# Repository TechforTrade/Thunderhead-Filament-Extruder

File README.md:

# Thunderhead Filament Extruder

The Thunderhead filament extruder is a  small scale extruder designed by Techfortrade that can be used for recycling PET plastic bottle flake directly into 3D printing filament. A special emphasis throughout the design has been placed on using affordable and easily attainable materials. This repository serves as a host for the documentation and code used with the machine. We are using GrabCAD Workbench for the hardware development and will place snapshots of the CAD files here on Github with each release. Current (though not necessarily stable) files can be accessed on our [GrabCAD partner space](https://workbench.grabcad.com/workbench/projects/gcvN9Xsi01SW-lFGhJRj_-4vqndCMFAaoUt_-UQBdidnVn#/space/gc8b8c582LagITdwrMEId6wysTlJX_nukUvWoRwEQ_1f4U).

#### The Thunderhead converts clean and dry PET flake into 3D printing Filament

# Table of Contents

- [Goals](#goals)
- [PET Plastic](#pet-plastic)
- [Safety and Liability](#safety-and-liability)
- [Building the Thunderhead](#building-the-thunderhead)
- [Software](#software)
- [Operation](#operation)
- [Contributing](#contributing)
- [Maintainers](#maintainers)
- [Acknowledgements](#acknowledgements)
- [License](#license)

## Goals
The Thunderhead is designed with the intent of making it possible to recycle plastic from the post consumer waste stream into 3D printing filament on a small scale with minimal start up capital required. This makes the following possible:
- Low cost 3D printing filament anywhere in the world
- Enable local capture of the value contained in waste plastic
- Access to expensive or hard to find items via 3D printing (eg. [Open Flexure Microscope](https://github.com/rwb27/openflexure_microscope))
- Small scale business opportunities without need for large amounts of capital
- Enable local recycling where it is otherwise not possible

## PET Plastic 
The Thunderhead is designed to extrude Polyethylene Terephthalate (PET or PETE) for the following reasons:

-  Prints  very well on printers such as the Retr3D
-  Easy to find nearly anywhere on the planet
-  Has good physical properties
-  Reasonably safe to work with, especially compared to ABS which often has Brominated Flame Retardants (BFR)

PET is easily identified by the following symbol usually located on the bottom on the bottle:

There are some challenges to working with PET plastic. A few these are described below. Follow the links to get more detailed information on these and other challenges:

* **Crystalization** - PET crystalizes when cooled slowly. To avoid making filament that is brittle like glass, a water bath is used.
* **Low Viscosity** - When PET melts it has a low viscosity and a low melt strength which makes it difficult to pull into a filament with an even diameter. The Thunderhead uses a cooling tube to help increase the viscosity and melt strength before the plastic leaves the extruder. The water bath also helps to 
* **Hygroscopicity** - PET pulls water out of the air and holds on to it. This water can cause problems during extrusion and printing such as air bubbles, foaming and degredation of the plastic.
* **Hydrolysis** - The polymer chains in PET can break down in the presence of water at elevated temperatures. When this happens, the viscosity of the melt is reduced, making it difficult to extrude. To Avoid this problem, the plastic flakes must be thoroughly dried just before extrusion. 

## Safety and Liability

You are responsible for your own safety. This machine is under development. Please see the text in the license regarding **Disclaimer of Warranties and Limitation of Liability**.

## Building the Thunderhead

Please refer to our [wiki](https://github.com/TechforTrade/Thunderhead-Filament-Extruder/wiki) for detailed information on building the Thunderhead. 

#### Major Tools Needed ####

Note that you don't necessarily have to own all of these tools. A local shop could do some of the work for you. Especially the lathe and milling work. See the Wiki for a more exhaustive list.

* Drill Press
* Metal Lathe - Threading the barrel and making the shaft for the gear box
* Welding (stick, oxy-acetalene, etc.) - For welding frames together
* 3D printer - Many of the complex parts in the machine are 3D printed
* Milling Machine (optional) - For milling flats into a few parts. Could be done with grinder and hand files though more time consuming.
* Horizontal band saw (optional) - For cutting stock metal to size. A hacksaw and vice will work, but will be slower.

#### Major Components of the Thunderhead - THIS NEEDS UPDATING

1. **Control Box** - Contains the power supply, Arduino, and other circuitry needed to operate the extruder. Note: The starve feeder, diameter sensors and spooler have their own control circuitry and communicate with the master Arduino via IIC.
2. **Starve Feeder**- Used to add flakes to the extruder at a constent rate. Subcomponents are:
   1. Hopper - Holdes flake ready to be extruded
   2. Vibratory Conveyer - Moves flake to the balance and keeps flake from bridging, and rat holing.
   3. Balance - Weighs out small portions of flake and then delivers them to the extruder at a constant rate. Feedback from the balance controls the vibratory conveyer.
3. **Auger Motor and Gear Box** - A large NEMA 42 stepper motor and 3:1 gear box with 3D printed gears. The stepper alows for speed control and the gearbox increases the torque on the auger.
4. **Extruder Body** - The extruder body has many components. The main components are:
   1. Feed Throat - Location where the plastic enters the barrel. Made with internal grooves to improve the feeding of the plastic into the barrel.
   2. Auger - A 1/2 in. diameter, 18 in. long wood auger used to convey the plastic through the barrel. NOTE: This is not designed for plastics extrusion and performs significantly worse than a plastic extrusion screw would. It is much less expensive though.
   3. Barrel - 1/2in I.D. DOM metal pipe through which the auger pushes the plastic. It has two heating zones that are heated by 104 watt 1/2 in. fiberglass insulated heating tape.
   4. Breaker plate - A small disk of metal with a number of holes drilled into it at the downstream end of the barrel. It acts to reduce the twist in the plastic that is caused by the screw, reducing what is called "screw beat" and improving the uniformity of the diameter. 
   5. Cooling tube - A brass tube at the end of the barrel that reduces the temperature of the plastic melt in order to increase its viscosity. The bend in the tube helps to aim the filament at the guide roller at the end of the water bath and improve roundness of the filament. It has two heating zones.
   6. Nozzle - determines diameter of melt as it leaves the extruder. Equiped with its own heating zone so that surface quality of the filament can be improved.
5. **Extruder Stand** - Supports the extruder and has a sheet metal enclosure to collect fumes given off by the extruder.
6. **Diameter Sensors** - Non contact laser diameter sensors with their own control electronics. The first is used to determine the diameter of the melt as it leaves the extruder and control the speed of the outfeed rollers in order to maintain a constant diameter. The second is used to monitor the final diameter and ensure that the set point of the first diameter sensor is correct.
7. **Outfeed Rollers** - Used to pull the filament through the water bath. Their speed determines the diameter of the filament. The rollers are controlled by the primary diameter sensor.
8. **Water Bath** - Used to cool the melt quickly. This is important because otherwise, the PET would neck down to a very small diameter or cool too slowly and crystalize. Crystalized plastic is too brittle to work with a 3D printer.
9. **Spooler** - Winds the filament up onto a spool. The spooler is still being worked on, early designs fought with the outfeed rollers and caused uneven filament diameters.

## Software

Please refer to our [wiki](https://github.com/TechforTrade/Thunderhead-Filament-Extruder/wiki) for detailed information on the use of the various bits of code kept in this repository.

Firmware must be installed on the Arduino to get the Thunderhead up and running:

- **Thunderware.ino** - for the Arduino Mega 2560 that controls the machine (located in the low voltage electronics enclosure)

## Operation

Detailed operation instructions with tips and trouble shooting are located in our [wiki](https://github.com/TechforTrade/Thunderhead-Filament-Extruder/wiki). The following summarizes basic operation. Video of this process can be found here.

#### Preparation

Before extruding, the clean PET flake must be dried. This must happen just before extruding because the PET will absorb water out of the air at room temperature. The current design incorporates a drying hopper that does this task. If you are using a simple hopper, you can dry the PET in a bench top oven (toaster oven) at a temperature between 150 and 170 °C for four hours. Do this in a well ventilated area. It is recomended to capture and vent the fumes with a fume hood and duct. Do not exceed 175 °C as the plastic will begin to degrade. Keep the flake in the oven until the extruder is ready to begin extruding so that the flake is exposed to room temperature air for as little time as possible.

#### Extruding

**Note:** This section is being updated as the firmware has changed. If you have imediate needs, contact us.

## Contributing

We'd love your help! You can contribute in many ways. Here are a few:

* Technical support on designs, code etc.
* Help improve the wiki and other documentation.
* Testing. Different Extrusion parameters, code, etc.
* Connect us with other interested individuals and groups.
* Donate! [Techfortrade](http://www.techfortrade.org/) is a non profit organization working to create business opportunities in low resource settings.

## On Going Work

All the of the most up to date CAD files can be found [here on our GrabCAD Workbench](https://workbench.grabcad.com/workbench/projects/gcvN9Xsi01SW-lFGhJRj_-4vqndCMFAaoUt_-UQBdidnVn#/space/gc8b8c582LagITdwrMEId6wysTlJX_nukUvWoRwEQ_1f4U). The following are a few ideas that we are hoping to pursue:

### Planned Improvements and Experiments ###

### Computer Vision Based Diameter Sensor###

We are working to develop a computervision based diameter sensor. It uses a Raspberry Pi and a USB webcam. The laser based diameter sensor we were developing had too many issues (low quality optics caused too much noise).   

#### Feedback Control####

When the non-contact diameter sensor is working we can get real time information on diameter. This will allow for the use of a PID controller connected to the outfeed. The goal is to eliminate the need for a printer based diameter sensor.

#### Drying hopper ####

The Drying hopper is currently in use in Kenya. Initial reports are very positive. The BOM is posted on the WIKI, but assembly instructions are not complete.

#### New Filament Support/Guiding Strategy ####
The shape and diameter of the filament is essentially set when the hot plastic
enters the water bath. Unwanted movement of the filament down stream from this
point can greatly impact the shape of the filament. New strategies for guiding
the filament in a controlled manner need to be explored. 

#### Nozzle Geometry and Drawdown ####
It may be fruitful to explore different nozzle geometries and the amount and
rate of drawdown. What are the optimal conditions for consistent filament?

#### Test Different Sources of PET ####
Not all PET resins are the same. By testing resins from various bottle sources
and even virgin pellets, it may be possible to determine whether or not some
sources have more desirable characteristics than others.

#### Melt Filter ####
A screen should be added just up stream of the breaker plate. This screen will
catch debris and improve the quality of the filament. A down side is that a melt filter may reduce, perhaps greatly, the output of the machine.

#### Explore potential additives

Desiccating agents such as CaO (quicklime) or even Portland cement might
possibly be added to scavenge water remaining in the melt, which would help
improve viscosity. Nucleating agents such as sodium benzoate and talc might be
used to encourage crystal growth, growing more numerous and smaller crystals
which may help to reduce the brittleness of crystalline polymer. Could this be a route to producing printable crystalline PET?

## Maintainers

[Matthew Rogge](https://github.com/Maaphoo) and [Michael Uttmark](https://github.com/biosafetylvl5) are currently the maintainers of this
repository.

## Acknowledgements

The following people and organizations provided valuable help and guidance over
the course of the project:

**Matt Clark** who provided hundreds of free man hours to assist with the re-design process.

**Frank Schoofs** who volunteered his material science expertise to assist with thermal modeling required to design heating and cooling sections of the extruder.

**Vasileios Grammatikakis** an electronics expert who has assisted with improvements to the Thunderhead electronics.

**Unilever plc.** whose PET specialists have provided insights into working with PET, drying, and testing.

## 

## License

This work is licensed under a <a rel="license" href="http://creativecommons.org/licenses/by-sa/4.0/">Creative Commons Attribution-ShareAlike 4.0 International License</a>.

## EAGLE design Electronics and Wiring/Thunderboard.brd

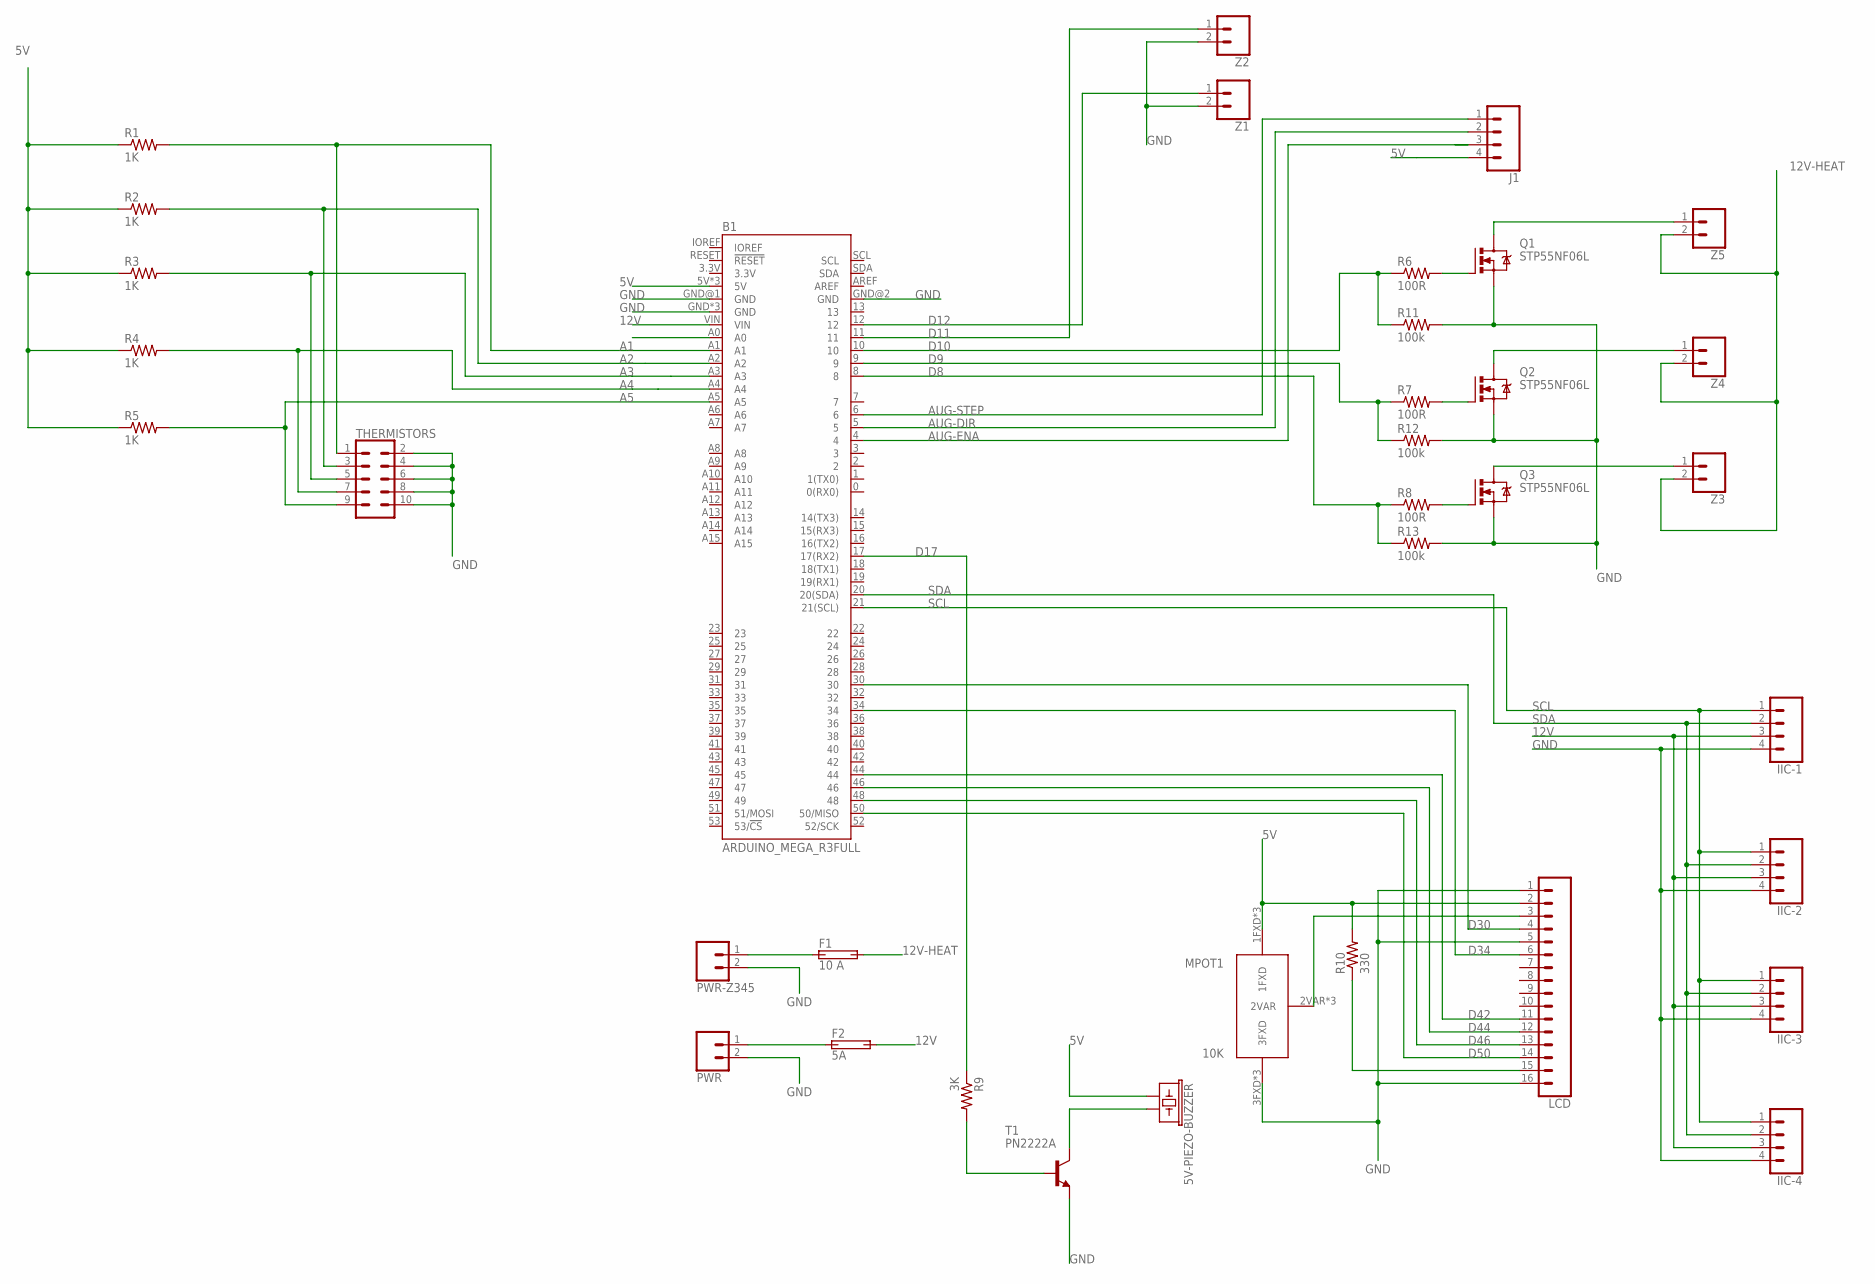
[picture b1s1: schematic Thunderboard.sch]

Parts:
5V-PIEZO-BUZZER: BUZZER-PTH; BUZZER-12MM
B1: ARDUINO_MEGA_R3FULL; ARDUINO_MEGA_NO_SILK
F1: 10 A; MINI-BLADE
F2: 5A; MINI-BLADE
IIC-1, IIC-2, IIC-3, IIC-4: CONN_04; 1X04
J1: CONN_04; 1X04
LCD: CONN_16; 1X16
MPOT1: 10K; POT-MULTI-PACKAGE
PWR: CONN_023.5MM; SCREWTERMINAL-3.5MM-2
PWR-Z345: CONN_023.5MM; SCREWTERMINAL-3.5MM-2
Q1, Q2, Q3: STP55NF06L; TO-220
R1, R2, R3, R4, R5: 1K; 0207/7
R6, R7, R8: 100R; 0207/7
R9: 3K; 0207/7
R10: 330; 0207/7
R11, R12, R13: 100k; 0207/7
T1: PN2222A; TO92-EBC
THERMISTORS: CONN_05X2NO_SILK; 2X5_NOSILK
Z1, Z2: CONN_02; 1X02
Z3, Z4, Z5: CONN_023.5MM; SCREWTERMINAL-3.5MM-2

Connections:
5V: 5V-PIEZO-BUZZER.+ (1), B1.5V, B1.5V@1 (5V), B1.5V@2 (5V), J1.4, LCD.2, MPOT1.1FXD, MPOT1.P$7 (1FXD), MPOT1.P$8 (1FXD), R1.1, R2.1, R3.1, R4.1, R5.1, R10.2
12V: B1.VIN, F2.2A (2), F2.2B (2), IIC-1.3, IIC-2.3, IIC-3.3, IIC-4.3
12V-HEAT: F1.2A (2), F1.2B (2), Z3.2, Z4.2, Z5.2
A1: B1.A1, R1.2, THERMISTORS.1
A2: B1.A2, R2.2, THERMISTORS.3
A3: B1.A3, R3.2, THERMISTORS.5
A4: B1.A4, R4.2, THERMISTORS.7
A5: B1.A5, R5.2, THERMISTORS.9
AUG-DIR: B1.5, J1.2
AUG-ENA: B1.4, J1.3
AUG-STEP: B1.6, J1.1
D8: B1.8, R8.1, R13.1
D9: B1.9, R7.1, R12.1
D10: B1.10, R6.1, R11.1
D11: B1.11, Z2.1
D12: B1.12, Z1.1
D17: B1.17 (17(RX2)), R9.1
D30: B1.30, LCD.4
D34: B1.34, LCD.6
D42: B1.44, LCD.11
D44: B1.46, LCD.12
D46: B1.48, LCD.13
D50: B1.50 (50/MISO), LCD.14
GND: B1.GND, B1.GND@1 (GND), B1.GND@2 (GND), B1.GND@3 (GND), B1.GND@4 (GND), IIC-1.4, IIC-2.4, IIC-3.4, IIC-4.4, LCD.1, LCD.5, LCD.16, MPOT1.3FXD, MPOT1.P$4 (3FXD), MPOT1.P$5 (3FXD), PWR.2, PWR-Z345.2, Q1.S, Q2.S, Q3.S, R11.2, R12.2, R13.2, T1.E, THERMISTORS.2, THERMISTORS.4, THERMISTORS.6, THERMISTORS.8, THERMISTORS.10, Z1.2, Z2.2
unnamed: 5V-PIEZO-BUZZER.- (2), T1.C
unnamed: R9.2, T1.B
unnamed: Q1.G, R6.2
unnamed: Q2.G, R7.2
unnamed: Q3.G, R8.2
unnamed: LCD.3, MPOT1.2VAR, MPOT1.P$1 (2VAR), MPOT1.P$3 (2VAR)
unnamed: Q1.D, Z5.1
unnamed: Q2.D, Z4.1
unnamed: Q3.D, Z3.1
unnamed: F1.1A (1), F1.1B (1), PWR-Z345.1
unnamed: LCD.15, R10.1
unnamed: F2.1A (1), F2.1B (1), PWR.1
SCL: B1.21 (21(SCL)), IIC-1.1, IIC-2.1, IIC-3.1, IIC-4.1
SDA: B1.20 (20(SDA)), IIC-1.2, IIC-2.2, IIC-3.2, IIC-4.2

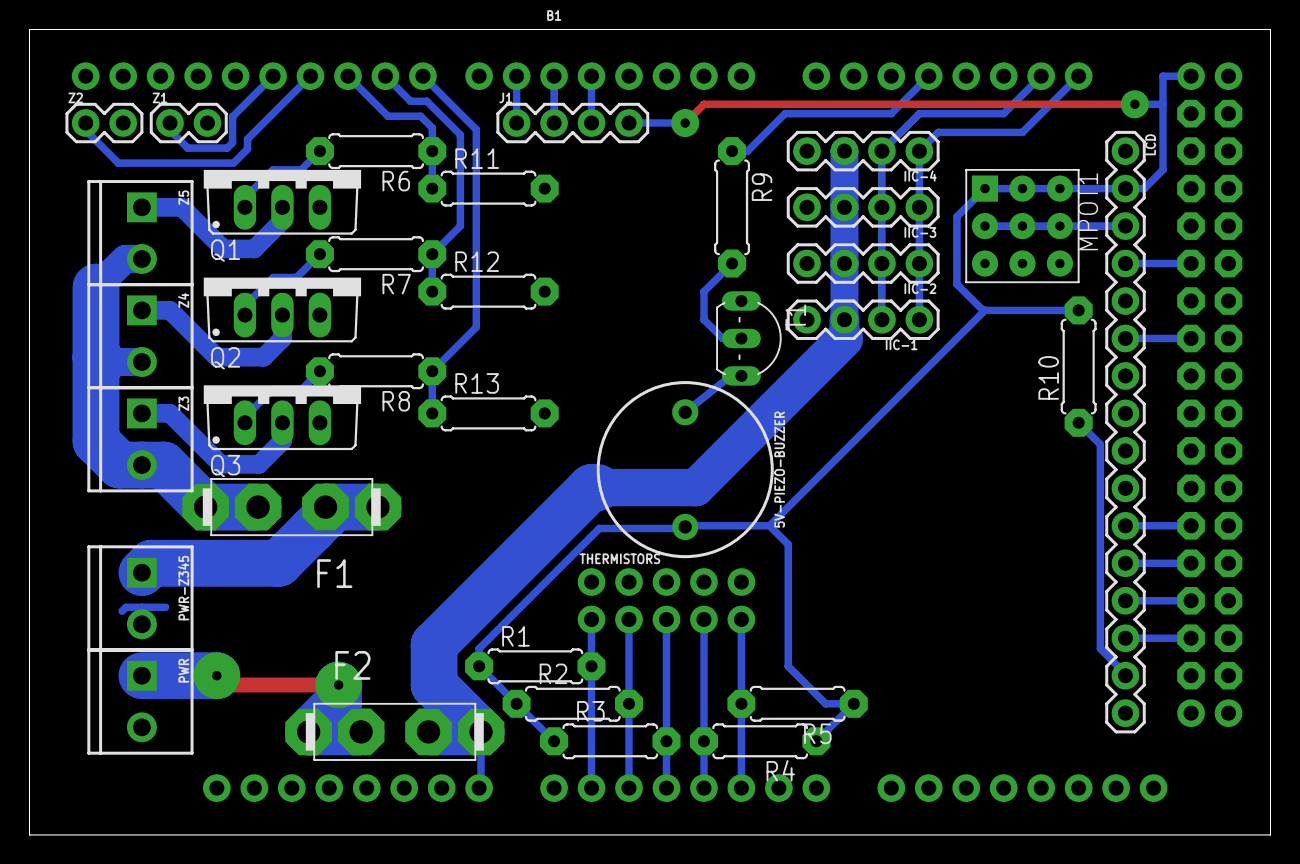
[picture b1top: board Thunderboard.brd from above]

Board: 2 copper layers, 84.1 x 54.6 mm, 36 parts (0 on the bottom side), 38 nets.

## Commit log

2016-09-03 Initial Commit :purple_heart:
2016-09-03 Initial Bulk Commit :heart:
2016-09-03 README Scaffold
2016-09-03 Added output diameter
2016-09-03 Added zone information
2016-09-03 Added stepper
2016-09-03 Added auger
2016-09-03 Added more zonal info
2016-09-04 Revised heating information
2016-09-04 Added Outfeed, spooler and waterbath
2016-09-04 Added acknowledgements
2016-09-04 Added potential improvements
2016-09-04 Added thermistors
2016-09-04 Added filament picture
2016-09-04 Formatting changes
2016-09-04 Added flow images
2016-09-05 Removed accidental content.
    The content under the "Users" section was a note to self, and does not reflect the views or opinions of TechforTrade in anyway.
    with 'origin/master'.
2017-12-15 Removed old CAD files and began playing with READEME.md
2017-12-15 Trying to figure out how to resize images
2017-12-15 Still Playing with Images...
2017-12-15 Guess I have to use HTML
2017-12-19 Added more to the README file and also added code files.
2017-12-19 Deleted assembly and images
2017-12-19 Fixed typo in README.md
2017-12-28 Added image of Thunderhead with components labeled.
2017-12-28 Additions to ReadMe
2017-12-28 Added ReadMe section about the parts of the extruder.
2017-12-28 Added the Extruder_Components.jpg image and bolded a few items in the README file
2017-12-29 Modified extruder components diagram and text. Switched to Open Office.
2017-12-29 Added section on operating the extruder.
2017-12-29 Trying to fix TOC
2017-12-29 Trying to fix Safety/Liability in TOC
2017-12-29 Changed heading to Safety and Liability
2018-02-03 adding video
2018-02-03 Added video thumbnail
2018-02-03 Changed name of thumb
2018-02-03 Changed image format
2018-02-05 Added images of Auger Motor and Gear Box parts.
2018-02-05 no message
2018-02-05 Fixing name of file
2018-02-05 Adding images
2018-02-05 Fixing name
2018-02-25 Adding images for Extruder body and some tools
2018-02-25 Adding a few Drawings
2018-02-26 Rotated image of Nail Punch
2018-02-28 Update README.md
    adding donate button
2018-02-28 Update README.md
    Fixing donate button
2018-07-16 Adding images for the Auger gear and motor.
2018-07-17 Fixing bugs in documentation scripts
2018-07-18 Updating images of the Auger gear box and motor.
2018-07-18 Updating image of auger gear box and motor
2018-07-19 updating extruder body images
2018-07-19 adding video frame
2018-07-19 Updating images in extruder body
2018-07-19 Updating extruder body.
2018-07-19 Update README.md
    Moved location of fume hood
2018-07-30 Updating images for stand and water bath.
2018-07-30 Adding images for extruder stand wiki.
2018-07-30 updating vid image for stand.
2018-07-31 Updating images for water bath.
2018-07-31 Updating water bath images.
2018-07-31 Correcting the water bath weldment drawings.
2018-08-18 Updating images for Vibratory Conveyor
2018-08-18 Adding video frame for vibratory conveyor stand.
2018-08-18 Adding images for Vibratory Conveyor.
2018-08-18 Adding video frame and main image for Vibratory Conveyor.
2018-08-18 updating video images. Fixed bug in scripts.
2018-08-27 updating images for primary diameter sensor
2018-08-27 adding video images for primary diameter sensor
2018-08-27 Adding images for QC diameter sensor
2018-08-28 Adding images for the outfeed.
2018-09-07 Adding images for balance
2018-12-06 Fix swapped numbers
2019-01-30 Adding the Thunderboard schematic and the general wiring schematic. Also adding some images used in the documentation.
2019-01-30 Just including the eagle project file.
2019-01-30 Updating the wiring schematic.
2019-01-31 Adding images for documentation.
2019-01-31 More images for documentation.
2019-01-31 Images for documentation.
2019-01-31 Pictures for documentation.
2019-01-31 Adding Wiring diagram image
2019-01-31 Adding PCB image
2019-02-01 Updating electronics files
2019-02-01 Adding datasheets.
2019-02-01 Adding images of work in Nairobi
2019-02-01 Adding image to wiki
2019-02-06 Adding more documentation images
2019-02-06 Adding more images
2019-02-21 Changes made after testing the Thunderboard. Switched from Tip120 to a power fet STP55NF06L.
2019-02-21 Setting default extrusion profile to all zeros. That will prevent the bad situation where the auger stepper begins turning and the barrel is still cold. Note that Preheat and Soak states are skipped 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
2019-11-15 Uploading more current image of machine.
2019-11-15 Added note about this version of the firmware
2019-11-15 Added note that the firmware is intended for use with the Thunderboard. This the first step after moving the Thunderboard compatable branch into the Master.
2019-11-15 Adding note to breadboard based version kept around for old versions of the extruder.
2019-11-15 Updating code so that the code in the master branch can handle both old and new versions of electionics using #define/#ifdef calls.
2019-11-15 Fixed a bug with the outfeed. Compiles but not tested.
2019-12-13 Updating some images while testing revisions to the documentation scripts
2019-12-14 Updating images
2019-12-15 Adding images mainly of hopper.
2019-12-15 Uploading images for high voltage electronics
2019-12-15 Adding images and files for low voltage electronics
2020-01-17 updating documentation
2020-01-18 Updating some images
2020-07-16 Adding bottle chopper image.
2020-07-24 Adding image of the Thunderboard with component outlines.

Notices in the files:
parts and their libraries:
SparkFun-Boards: Licensing: Creative Commons ShareAlike 4.0 International - https://creativecommons.org/licenses/by-sa/4.0
